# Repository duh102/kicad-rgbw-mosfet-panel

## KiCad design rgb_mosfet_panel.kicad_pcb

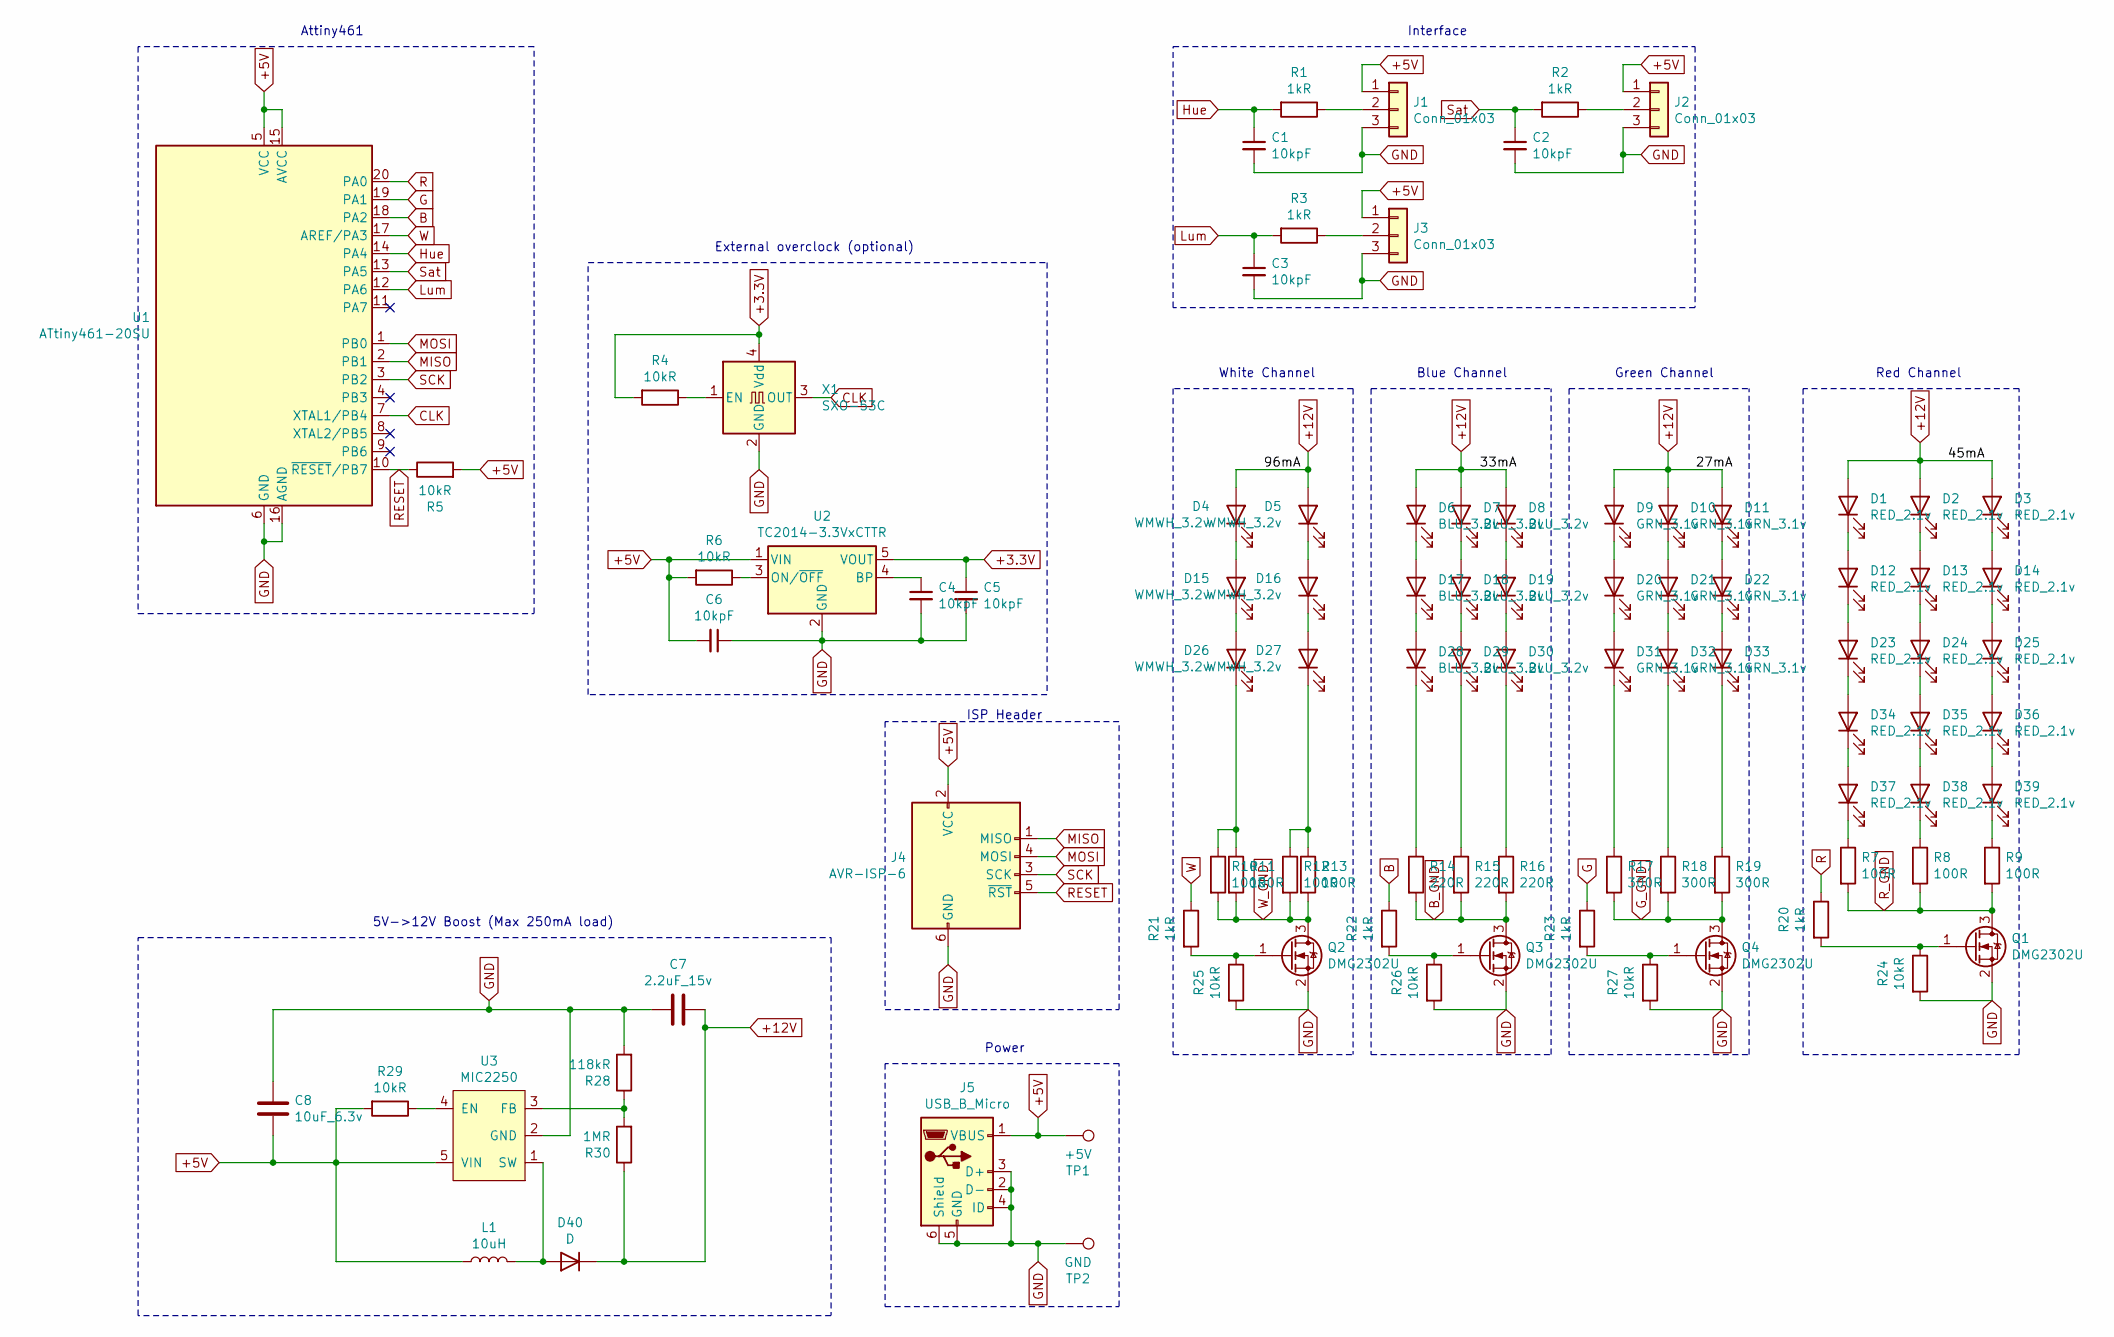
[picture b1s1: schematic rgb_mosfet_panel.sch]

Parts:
C1, C2, C3, C4, C5, C6: 10kpF; C_0603_1608Metric
C7: 2.2uF_15v; C_0603_1608Metric
C8: 10uF_6.3v; C_0603_1608Metric
D1, D2, D3, D12, D13, D14, D23, D24, D25, D34, D35, D36, D37, D38, D39: RED_2.1v; LED_0805_2012Metric
D4, D5, D15, D16, D26, D27: WMWH_3.2v; LED_Yuji_5730
D6, D7, D8, D17, D18, D19, D28, D29, D30: BLU_3.2v; LED_0805_2012Metric
D9, D10, D11, D20, D21, D22, D31, D32, D33: GRN_3.1v; LED_0805_2012Metric
D40: D; D_SMA
J1, J2, J3: Conn_01x03; SolderJumper-3_P1.3mm_Open_Pad1.0x1.5mm_NumberLabels
J4: AVR-ISP-6; PinHeader_2x03_P2.54mm_Vertical_SMD
J5: USB_B_Micro; USB_Micro_B_Female_10118194-0001LF
L1: 10uH; L_Taiyo-Yuden_NR-50xx
Q1, Q2, Q3, Q4: DMG2302U; SOT-23
R1, R2, R3, R20, R21, R22, R23: 1kR; R_0805_2012Metric
R4, R5, R6, R24, R25, R26, R27, R29: 10kR; R_0805_2012Metric
R7, R8, R9, R10, R11, R12, R13: 100R; R_0805_2012Metric
R14, R15, R16: 220R; R_0805_2012Metric
R17, R18, R19: 300R; R_0805_2012Metric
R28: 118kR; R_0805_2012Metric
R30: 1MR; R_0805_2012Metric
TP1: +5V; TestPoint_Pad_2.5x2.5mm
TP2: GND; TestPoint_Pad_2.5x2.5mm
U1: ATtiny461-20SU; TSSOP-20_4.4x6.5mm_P0.65mm
U2: TC2014-3.3VxCTTR; SOT-23-5
U3: MIC2250; TSOT-23-5
X1: SXO-53C; Oscillator_SMD_TXC_7C-4Pin_5.0x3.2mm

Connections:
+3.3V: C5.1, R4.2, U2.5 (VOUT), X1.4 (Vdd)
+5V: C6.2, C8.2, J1.1, J2.1, J3.1, J4.2 (VCC), J5.1 (VBUS), L1.1, R5.2, R6.2, R29.2, TP1.1, U1.5 (VCC), U1.15 (AVCC), U2.1 (VIN), U3.5 (VIN)
+12V: C7.2, D1.2 (A), D2.2 (A), D3.2 (A), D4.2 (A), D5.2 (A), D6.2 (A), D7.2 (A), D8.2 (A), D9.2 (A), D10.2 (A), D11.2 (A), D40.1 (K), R30.1; also elsewhere on the board
B: R22.1, U1.18 (PA2)
B_GND: Q3.3 (D), R14.2, R15.2, R16.2
CLK: U1.7 (XTAL1/PB4), X1.3 (OUT)
G: R23.1, U1.19 (PA1)
GND: C1.2, C2.2, C3.2, C4.2, C5.2, C6.1, C7.1, C8.1, J1.3, J2.3, J3.3, J4.6 (GND), J5.2 (D-), J5.3 (D+), J5.4 (ID), J5.5 (GND), J5.6 (Shield), Q1.2 (S), Q2.2 (S), Q3.2 (S), Q4.2 (S), R24.2, R25.2, R26.2, R27.2, R28.2, TP2.1, U1.6 (GND), U1.16 (AGND), U2.2 (GND), U3.2 (GND), X1.2 (GND); also elsewhere on the board
G_GND: Q4.3 (D), R17.2, R18.2, R19.2
Hue: C1.1, R1.2, U1.14 (PA4)
Lum: C3.1, R3.2, U1.12 (PA6)
MISO: J4.1 (MISO), U1.2 (PB1)
MOSI: J4.4 (MOSI), U1.1 (PB0)
unnamed: C4.1, U2.4 (BP)
unnamed: D1.1 (K), D12.2 (A)
unnamed: D10.1 (K), D21.2 (A)
unnamed: D11.1 (K), D22.2 (A)
unnamed: D12.1 (K), D23.2 (A)
unnamed: D13.1 (K), D24.2 (A)
unnamed: D2.1 (K), D13.2 (A)
unnamed: D14.1 (K), D25.2 (A)
unnamed: D3.1 (K), D14.2 (A)
unnamed: D15.1 (K), D26.2 (A)
unnamed: D4.1 (K), D15.2 (A)
unnamed: D16.1 (K), D27.2 (A)
unnamed: D5.1 (K), D16.2 (A)
unnamed: D17.1 (K), D28.2 (A)
unnamed: D6.1 (K), D17.2 (A)
unnamed: D18.1 (K), D29.2 (A)
unnamed: D7.1 (K), D18.2 (A)
unnamed: D19.1 (K), D30.2 (A)
unnamed: D8.1 (K), D19.2 (A)
unnamed: D20.1 (K), D31.2 (A)
unnamed: D9.1 (K), D20.2 (A)
unnamed: D21.1 (K), D32.2 (A)
unnamed: D22.1 (K), D33.2 (A)
unnamed: D23.1 (K), D34.2 (A)
unnamed: D24.1 (K), D35.2 (A)
unnamed: D25.1 (K), D36.2 (A)
unnamed: D26.1 (K), R10.1, R11.1
unnamed: D27.1 (K), R12.1, R13.1
unnamed: D28.1 (K), R14.1
unnamed: D29.1 (K), R15.1
unnamed: D30.1 (K), R16.1
unnamed: D31.1 (K), R17.1
unnamed: D32.1 (K), R18.1
unnamed: D33.1 (K), R19.1
unnamed: D34.1 (K), D37.2 (A)
unnamed: D35.1 (K), D38.2 (A)
unnamed: D36.1 (K), D39.2 (A)
unnamed: D37.1 (K), R7.1
unnamed: D38.1 (K), R8.1
unnamed: D39.1 (K), R9.1
unnamed: D40.2 (A), L1.2, U3.1 (SW)
unnamed: J1.2, R1.1
unnamed: J2.2, R2.1
unnamed: J3.2, R3.1
unnamed: Q1.1 (G), R20.2, R24.1
unnamed: Q2.1 (G), R21.2, R25.1
unnamed: Q3.1 (G), R22.2, R26.1
unnamed: Q4.1 (G), R23.2, R27.1
unnamed: R4.1, X1.1 (EN)
unnamed: R6.1, U2.3 (ON/~OFF~)
unnamed: R28.1, R30.2, U3.3 (FB)
unnamed: R29.1, U3.4 (EN)
R: R20.1, U1.20 (PA0)
RESET: J4.5 (~RST), R5.1, U1.10 (~RESET~/PB7)
R_GND: Q1.3 (D), R7.2, R8.2, R9.2
SCK: J4.3 (SCK), U1.3 (PB2)
Sat: C2.1, R2.2, U1.13 (PA5)
W: R21.1, U1.17 (AREF/PA3)
W_GND: Q2.3 (D), R10.2, R11.2, R12.2, R13.2

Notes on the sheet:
5V->12V Boost (Max 250mA load)
Attiny461
White Channel
Blue Channel
Green Channel
Red Channel
ISP Header
Power
External overclock (optional)
Interface

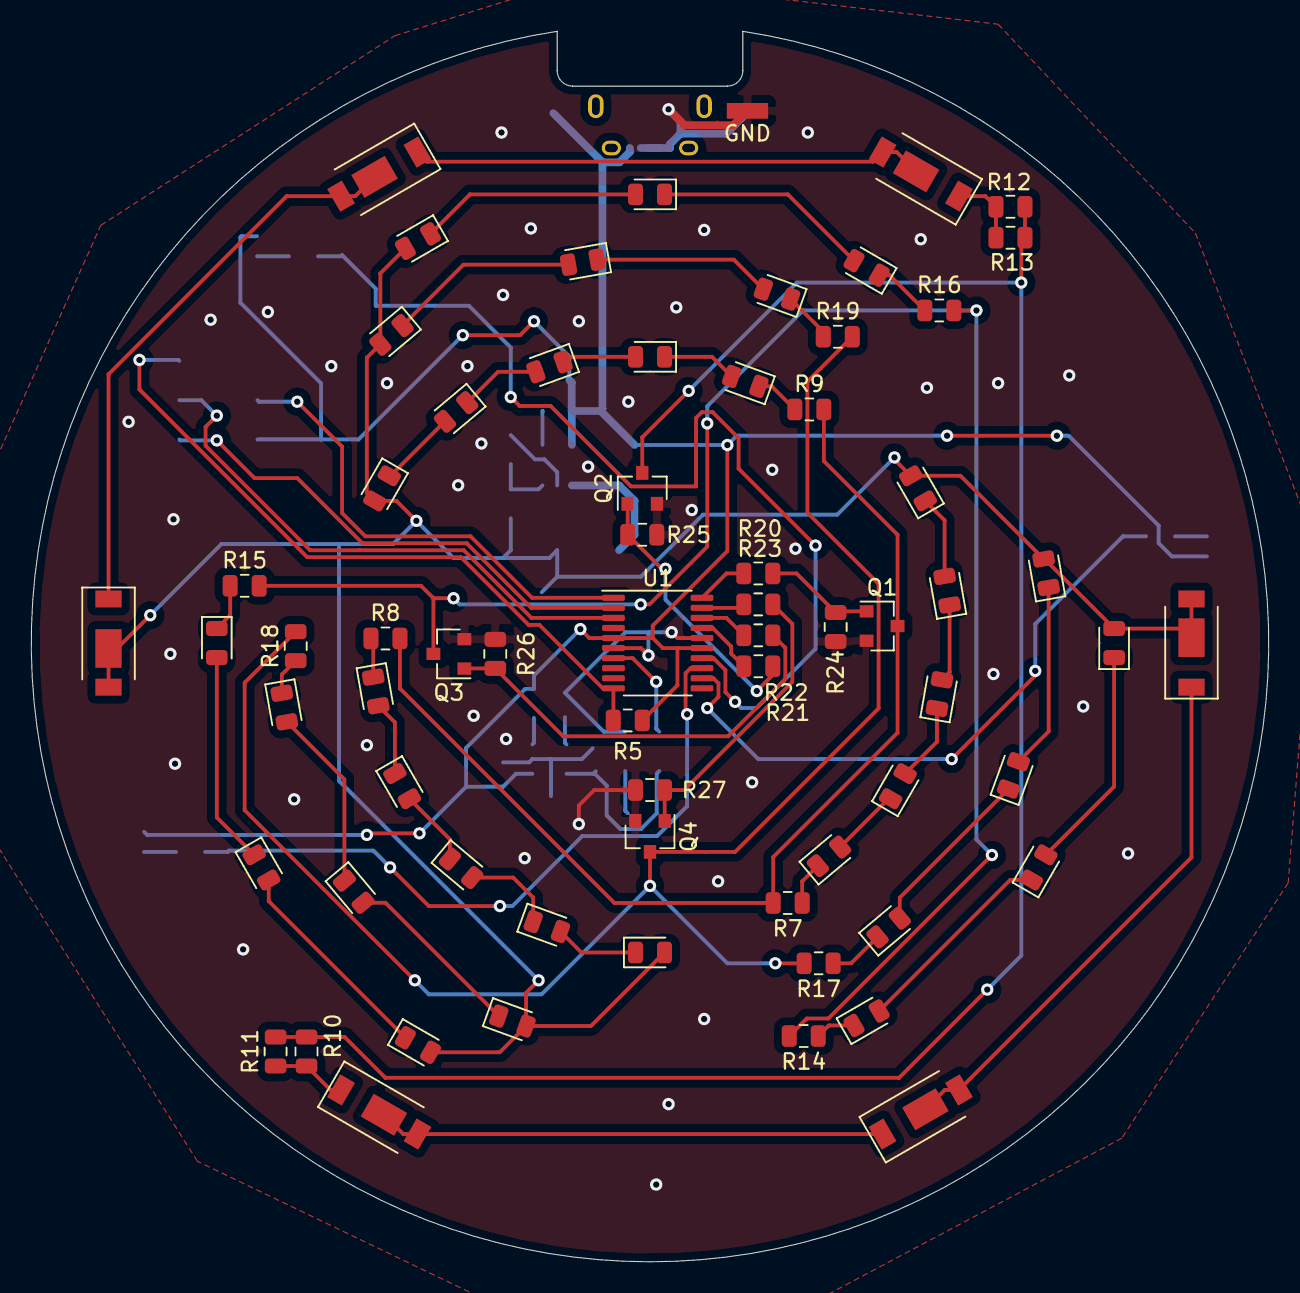
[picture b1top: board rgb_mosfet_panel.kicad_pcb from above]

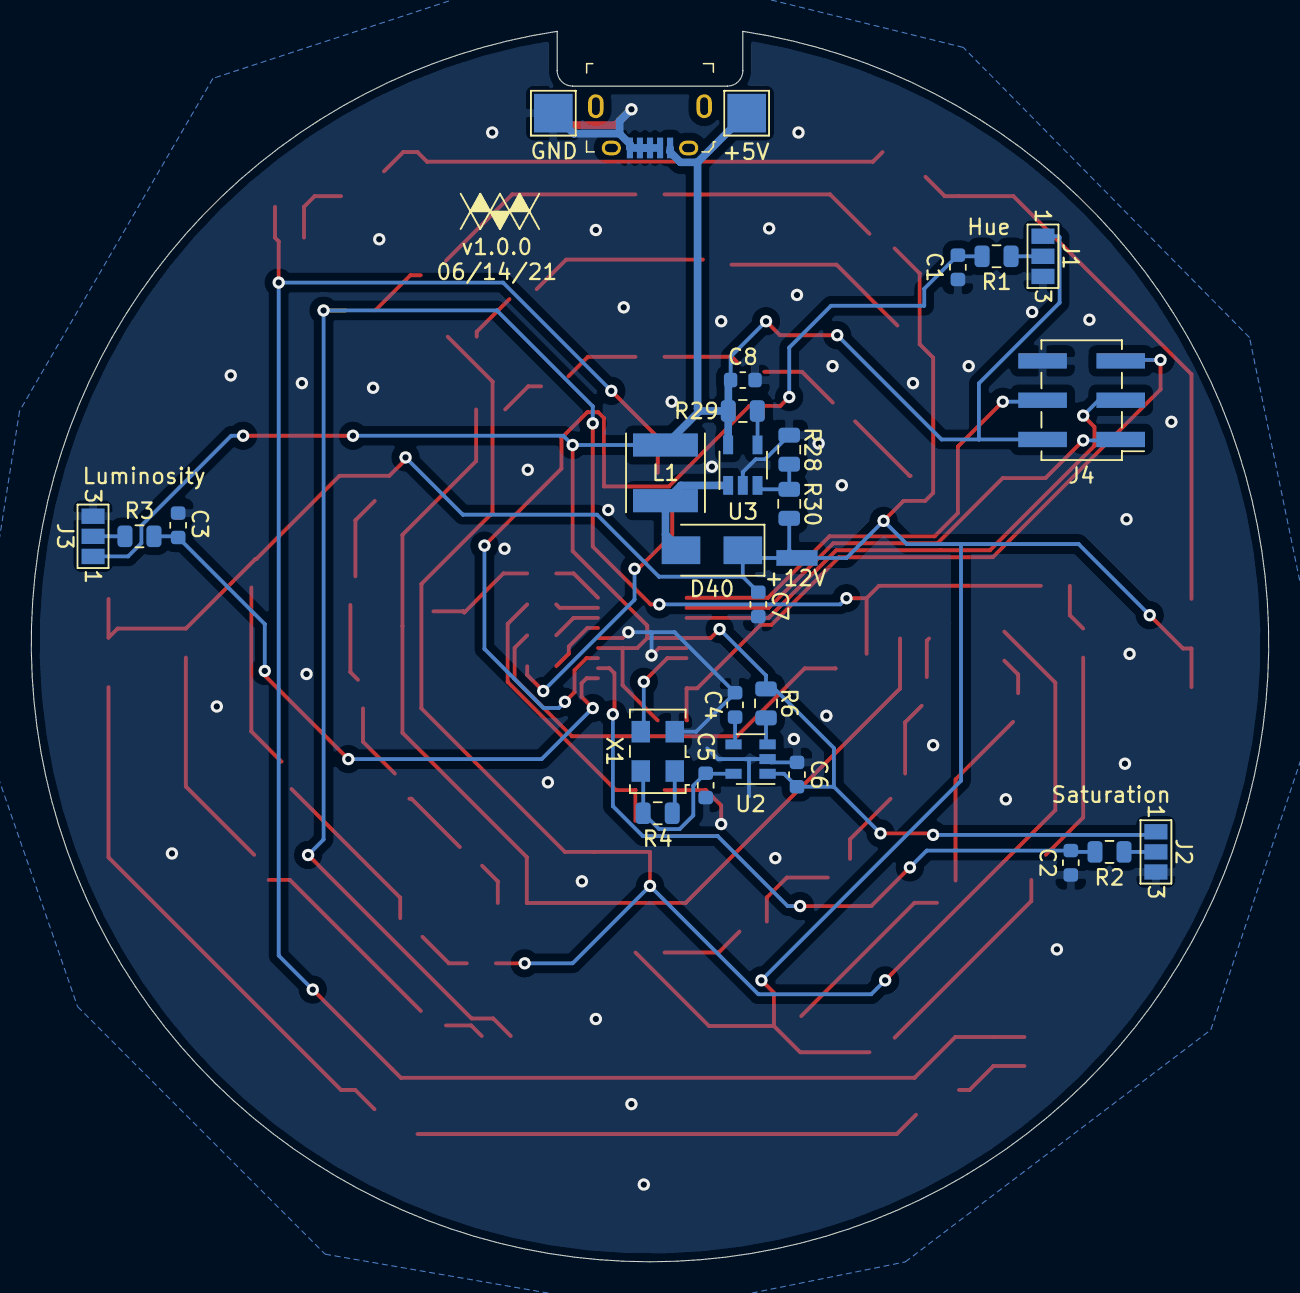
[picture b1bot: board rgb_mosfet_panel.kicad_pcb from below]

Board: 2 copper layers, 80.0 x 79.5 mm, 96 parts (29 on the bottom side), 72 nets.

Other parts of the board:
+12V: Test_Point_2.67x1.02mm
GND: Test_Point_2.67x1.02mm

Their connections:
+12V: +12V.1; also elsewhere on the board
GND: GND.1; also elsewhere on the board

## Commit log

2021-01-25 Add ISP header
2021-01-25 Add some rounds to blind corners
2021-02-05 Move around boost to hopefully work
2021-06-28 Update to use MIC2250
